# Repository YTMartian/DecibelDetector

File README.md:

# ESP32-C3 数字分贝检测器（INMP441 + 74HC595）

**PCB REV4 集成版 · 固件 v2.2 · 探测程序 v3 · 2026-10**

> **定位**：DIY 环境噪声监测与学习项目。它输出的是**估算 dB(A)**，不是经检定/校准的标准声级计，不能用于噪声合规判定或法律用途。

## 快速开始

1. 把 ESP32-C3 插进 U1-L/U1-R 两个 2×8 母座：**USB-C 朝下、芯片朝自己、5V 在左下角**。显示屏装到正面 JDISP_IN / JDISP_AUX，麦克风装到背面 JMIC。**先核对显示屏 5 脚顺序**（板上丝印：`LCD: CHECK INPUT PAD ORDER`），接反 VCC/GND 可能损坏模块。
2. Arduino IDE：安装 `esp32 by Espressif Systems` 3.x，板子选 `ESP32C3 Dev Module`，**Tools → USB CDC On Boot → Enabled**。
3. 烧 `firmware/Display_595_Probe`，看数码管：每组 profile 先显示 `1234`，再显示四位 `0/1`。找到 `1234` 正确的那组，记下四位。
4. 把四位填进主程序的四个 `constexpr bool`，必要时再填 `SEGMENT_MAP`，烧 `firmware/SoundMeter_595_ESP32C3`。
5. 接上麦克风，串口应出现 `A_est` / `Z_est` / `rmsA` / `rmsZ`；说话或拍手时数值应明显变化。

## 1. 能做什么

- INMP441 以 I²S **48 kHz、32-bit 槽、立体声**采集；`L/R` 接地，只使用左声道。
- ESP32-C3 计算**估算 A 计权声级**（dB(A)）和未计权声压级（Z），每 0.5 s 刷新四位数码管，同时从串口输出 A/Z/RMS。
- 显示驱动是**两片级联 74HC595**（一片段码、一片位选），不是 TM1637；不需要 TM1637 库。
- 显示极性、字节顺序、数字左右顺序、段码脚位都可配置；附带探测程序帮助确定。
- PCB 为**半集成载板**：ESP32 仍插在正面 2×8 母座；显示屏和麦克风直接装在 PCB 的焊盘/插座上，不再使用 J1/J2 短线。USB-C 从底边缺口朝外，麦克风在背面拾音。

## 2. 当前状态

| 项目 | 状态 |
|---|---|
| 显示屏 + 595 驱动 | 实物调通 |
| INMP441 I²S 采集 | 实物调通 |
| 串口 A/Z/RMS 输出 | 实物调通（需 `USB CDC On Boot = Enabled`） |
| 绝对声压级校准 | **未做**，`CALIBRATION_OFFSET_DB = 0` |
| PCB REV4 打样 / KiCad DRC / 嘉立创 DFM | **未做** |
| 外壳、USB 插头外壳宽度、排针高度 | **未实测** |

测量不确定度主要来自：INMP441 灵敏度公差 ±3 dB、约 33 dB(A) 的等效输入噪声、近似的 A 计权、未校准、供电/显示耦合。**不要把绝对读数和标准限值直接比较。**

## 3. 硬件

### 3.1 物料

| 材料 | 数量 | 说明 |
|---|---:|---|
| ESP32-C3 SuperMini | 1 | USB-C，优先已焊排针版 |
| INMP441 I²S 麦克风模块 | 1 | 6 引脚，**只用 3.3V** |
| 四位 LED 数码管模块 | 1 | 两片 74HC595 级联；按实物引脚 |
| PCB REV4 | 1 | 81.28 × 60.96 mm，双层 1.6 mm |
| 1×8 母排针 | 2 | 2.54 mm，排距 15.24 mm |
| 1×5 母排针 | 2 | 显示屏两排 5 孔 |
| 6 根短线或对应插座 | 1 | 麦克风 JMIC（2×3 焊盘） |
| M2.2 螺丝 + 绝缘柱 | 4 | 显示屏定位 |
| M3 螺丝 + 绝缘柱 | 4 | 主板固定 |
| 杜邦线 | 若干 | 显示屏/麦克风转接 |
| USB-C **数据**线 | 1 | 能烧录的线 |
| 100 nF + 10 µF | 可选 | 供电/显示干扰大时加在 3.3V 附近 |

本项目没有独立的 `BOM.csv`/`netlist.csv`；板级连接以 PCB 丝印和本文表格为准，具体排针/座子按你手里的模块选。

### 3.2 显示屏：JDISP_IN / JDISP_AUX

正面显示屏区域有两排 5 孔：

- 右侧 **JDISP_IN** 是电气连接（从上到下）：

  | JDISP_IN | 信号 | ESP32-C3 |
  |---:|---|---|
  | 1 | VCC | 3V3 |
  | 2 | SCLK | GPIO7 |
  | 3 | RCLK | GPIO10 |
  | 4 | DIO | GPIO3 |
  | 5 | GND | GND |

- 左侧 **JDISP_AUX** 的 5 个孔**没有连接任何网络**，只作机械支撑/备用；不要把它当电源或信号。
- 四角有 4 个 **M2.2** 定位孔，对应显示屏模块的安装柱。

> **板上丝印明确写着 `LCD: CHECK INPUT PAD ORDER`。** 插屏前逐脚核对显示模块的 5 脚顺序是否与 `VCC/SCLK/RCLK/DIO/GND` 一致；不一致必须做转接/换线序，**不能硬插**，否则可能把 VCC 和 GND 接反。

### 3.3 麦克风：背面 JMIC

背面 `JMIC` 是 2×3 焊盘，按背面丝印逐脚连接：

| 位置 | 信号 | ESP32-C3 |
|---|---|---|
| 上排 | GND | GND |
| 上排 | VDD | 3V3 |
| 上排 | SD | GPIO6 |
| 下排 | L/R | GND |
| 下排 | WS | GPIO5 |
| 下排 | SCK | GPIO4 |

- INMP441 的 `L/R` 必须接 GND（选左声道）；悬空会导致声道错位或无声。
- 麦克风装在**背面**，声孔朝外；丝印：`MIC BACK ONLY` / `PORT FACES OUT`。
- 如果模块引脚间距和 JMIC 不一致，用短线按丝印连接，不要强行弯脚。

### 3.4 ESP32-C3 安装方向（关键）

拿起 PCB **正面朝自己，USB-C 指向下方底边的缺口**，开发板的**芯片也朝自己**。此时两侧从上到下的引脚应为：

| 排针位置 | 左侧 U1-L | 右侧 U1-R |
|---:|---|---|
| 1 | GPIO0 | GPIO21 |
| 2 | GPIO1 | GPIO20 |
| 3 | GPIO2 | GPIO10 |
| 4 | GPIO3 | GPIO9 |
| 5 | GPIO4 | GPIO8 |
| 6 | 3V3 | GPIO7 |
| 7 | GND | GPIO6 |
| 8 | 5V（不接） | GPIO5 |

即 **5V 应落在左下角**。安装前按实物丝印再确认一次；插反可能把 5V 灌到 GPIO/3V3，损坏模块。

### 3.5 电源与地

- INMP441 和显示逻辑都用 **3.3V**；不要把 5V 接到 INMP441 或显示模块的信号侧。
- 显示模块即使标称 5V，也优先用 3.3V 测试：亮度会低一些，但 GPIO 电平安全。
- 所有模块共地；电源轨先确认导通。
- 5V 焊盘不接任何模块，板子由 ESP32 的 USB-C 供电。

## 4. PCB REV4（集成版）

- 外形：**81.28 × 60.96 mm**，双层 FR-4，1.6 mm，1 oz 铜。
- USB-C 避让缺口：底边 `x = 34.036～46.228 mm`，`y = 53.340～60.960 mm`，即 **12.192 × 7.620 mm**；缺口在 ESP32 正下方。
- 4 个 M3 孔：`(5.08,5.08)`、`(76.2,5.08)`、`(5.08,55.88)`、`(76.2,55.88)`，直径 3.2 mm。
- 显示屏 4 个 M2.2 孔：`(20.32,8.636)`、`(20.32,25.908)`、`(54.864,8.636)`、`(54.864,25.908)`。
- 显示屏两排 5 孔：右侧 `JDISP_IN`（电气）与左侧 `JDISP_AUX`（未连网络），孔距 2.54 mm。
- ESP32 2×8 母座：排距 15.24 mm，同列 2.54 mm，钻孔 1.0 mm。
- 麦克风 `JMIC`：背面 2×3 焊盘，2.54 mm 间距，两排相距 7.62 mm。

文件：

- `source/SoundMeter_Integrated_C3_595_REV4.kicad_pcb`：可编辑 KiCad PCB（**不含** `.kicad_sch` 原理图）。
- `gerber/`：9 个 Gerber / 钻孔文件，KiCad 默认命名（`SoundMeter-F_Cu.gtl`、`-B_Cu.gbl`、`-F_Mask.gts`、`-B_Mask.gbs`、`-F_Silkscreen.gto`、`-B_Silkscreen.gbo`、`-Edge_Cuts.gko`、`-PTH.drl`、`-NPTH.drl`）。
- `Gerber_打样前先核对.zip`：上面 9 个文件打好的包，可直接上传嘉立创。
- `preview/Integrated_PCB_Front_Back.png`：正反面安装预览。

> **REV4 相对 v3**：显示屏和麦克风改为板载安装，不再有 J1/J2 短线；板深从 55.88 增加到 60.96，USB 缺口移到 ESP32 下方并加深到 7.62 mm。**不能复用 v3 的 Gerber。**

制板前：

1. 在 KiCad 里跑一次官方 **DRC**；本项目尚未跑过。
2. 上传 Gerber 到嘉立创后，在 2D/3D 预览确认 **USB 缺口被识别成单块异形板**、钻孔和焊盘完整。
3. 用实物 USB-C 插头核对缺口宽度（约 12.19 mm）和插头塑胶外壳；用实物排针核对 ESP32 插座高度。
4. 用实物显示屏核对两排 5 孔的间距和 4 个 M2.2 定位孔；**先核对 5 脚顺序**。
5. 嘉立创参数：双层、FR-4、1.6 mm、1 oz、绿色阻焊、常规表面处理；**不贴片**，手工焊排针/母座。

## 5. 软件环境

- **Arduino IDE 2.x**。
- 开发板核心：`esp32 by Espressif Systems` **3.x**（3.0 及以上）。
- 开发板：`ESP32C3 Dev Module`。
- **Tools → USB CDC On Boot → Enabled**（关键）。
- 不需要 TM1637 库；`ESP_I2S.h` 随 ESP32 核心提供。
- 串口监视器 115200（原生 USB CDC 的“波特率”实际不影响通信，保持默认即可）。

### 为什么必须开 USB CDC On Boot

ESP32-C3 SuperMini 没有 CH340/CP2102，USB-C 直接接芯片内置的 **USB Serial/JTAG**：

| 设置 | `Serial` 连到 | 结果 |
|---|---|---|
| **Enabled** | USB Serial/JTAG（GPIO18/19） | 电脑出现虚拟串口，`Serial.print` 能到监视器 |
| Disabled | UART0（GPIO20/21） | USB 口收不到应用输出；监视器全空，发字符还可能把 IDE/USB 卡住 |

这是**编译期选项**（`ARDUINO_USB_CDC_ON_BOOT`），改完必须**重新上传**。打开后 COM 号可能变化，重新选端口；先打开串口监视器再按 RST，能抓到启动日志。

> 固件里的串口输出已改成**非阻塞**：监视器没开或端口不对时只是丢数据，不会再把设备卡死。但 `USB CDC On Boot` 仍然要开，否则根本收不到数据。

## 6. 调试步骤

### 6.1 只装显示屏：`Display_595_Probe`

先不装麦克风，烧 `firmware/Display_595_Probe`（显示屏装到 JDISP_IN，JDISP_AUX 可空）。

- 16 组 profile 自动轮换，每组 2.5 s：
  - 前 **1.0 s** 显示 `1234`；
  - 后 **1.5 s** 显示四位 `0/1`，顺序为：

    ```text
    SEG_LOW  DIGIT_HIGH  SEG_FIRST  REVERSE
    ```

- 看到 `1234` 从左到右正确显示时，记下紧接着的四位。例如显示 `1 0 1 0`：

  ```cpp
  constexpr bool SEGMENT_ACTIVE_LOW = true;
  constexpr bool DIGIT_ACTIVE_HIGH  = false;
  constexpr bool SEGMENT_FIRST      = true;
  constexpr bool REVERSE_DIGITS     = false;
  ```

- 如果 `1234` 显示成 `4321`，按 `4` 翻转 `REVERSE_DIGITS`；如果四位全亮，按 `2` 翻转位极性；如果七段全亮，按 `1` 翻转段极性；如果段和位明显串了，按 `3` 翻转字节顺序。

**段码脚位不是标准 Q0=a…Q7=dp 时**：

- 串口发 `s` 进入段扫描，每 1.5 s 换一个原始段输出 `Q0…Q7`；
- 记下每个 `Qn` 实际点亮的是 `a/b/c/d/e/f/g/dp` 哪一段；
- 填主程序的 `SEGMENT_MAP`（方向是**逻辑段 → Q 编号**）：

  ```cpp
  // 例：Q0→dp, Q1→g, Q2→f, Q3→e, Q4→d, Q5→c, Q6→b, Q7→a
  constexpr uint8_t SEGMENT_MAP[8] = {7,6,5,4,3,2,1,0};
  ```

- 串口不可用时，数码管仍会自动显示四位的 profile 结果，**不依赖串口输入**；段扫描才需要串口命令。

可选串口命令：

| 键 | 作用 |
|---|---|
| `1` | 翻转 `SEGMENT_ACTIVE_LOW` |
| `2` | 翻转 `DIGIT_ACTIVE_HIGH` |
| `3` | 翻转 `SEGMENT_FIRST` |
| `4` | 翻转 `REVERSE_DIGITS` |
| `s` | 段扫描 Q0～Q7 |
| `d` | 位扫描 D0～D3 |
| `x` | 冻结当前 profile |
| `p` | 重新开始自动轮换 |
| `h` | 帮助 |

### 6.2 烧主程序：`SoundMeter_595_ESP32C3`

1. 把 6.1 得到的四个常量填进主程序顶部；非标准段序再填 `SEGMENT_MAP`。
2. 烧录。上电会显示 `8888` 约 0.5 s，然后清屏；前 1 秒是滤波器预热，约 1.5 秒后出第一个数。
3. 串口应出现类似：

```text
ESP32-C3 / INMP441 / 74HC595 sound meter (estimated, not certified)
Display profile: segmentLow=1 digitHigh=1 segmentFirst=1 reverseDigits=0
Segment map a..dp -> Q0,1,2,3,4,5,6,7
Sound display: estimated dB(A), rate=48000Hz, calibration offset=0.0 dB
A_est=62.3 dB(A)  Z_est=64.7 dB SPL  rmsA=0.000...  rmsZ=0.000...
```

4. 装好麦克风，对着它说话或拍手：`rmsZ` 应明显变化，`A_est`/`Z_est` 跟着上升。安静房间读数大约 30～40 dB(A) 是正常的（INMP441 自噪声约 33 dB(A)），不要强行清零。

### 6.3 串口没有输出 / IDE 卡住

1. 确认 **Tools → USB CDC On Boot = Enabled**，重新上传。
2. 拔插 USB，重新选 COM 口；ESP32-C3 原生 USB 有时会出现两个端口，换另一个试。
3. 先打开串口监视器，再按板子 RST（或拔插 USB），让启动横幅在监视器已打开时打印。
4. 确认选的是应用的 USB CDC 口，而不是下载模式/其他串口。
5. 如果旧版 ESP32 核心在输入字符时仍卡住：升级到最新 3.x（新版 `HWCDC` 对 USB 写有超时保护）；或干脆不发串口命令，直接用数码管显示的四位 profile。

## 7. 固件配置

修改 `firmware/SoundMeter_595_ESP32C3/SoundMeter_595_ESP32C3.ino` 顶部后重新编译上传：

| 常量 | 默认 | 说明 |
|---|---|---|
| `SEGMENT_ACTIVE_LOW` | `true` | 段输出低电平点亮 |
| `DIGIT_ACTIVE_HIGH` | `true` | 位选高电平点亮 |
| `SEGMENT_FIRST` | `true` | 先发送段码字节 |
| `REVERSE_DIGITS` | `false` | 位选 bit3 为最左位 |
| `SEGMENT_MAP[8]` | `{0,1,2,3,4,5,6,7}` | 逻辑 `a..dp` → 原始 `Q0..Q7` |
| `SHOW_A_WEIGHTED` | `true` | `true` 显示 A 计权；`false` 显示未计权 |
| `CALIBRATION_OFFSET_DB` | `0.0` | 没有参考仪器时保持 0 |
| `SAMPLE_RATE_HZ` | `48000` | A 计权系数按 48 kHz 设计 |
| `DISPLAY_INTERVAL_MS` | `500` | 显示/统计窗口 |

**不要单独把 `SAMPLE_RATE_HZ` 改成 16000 或 32000** 而不重新设计 A 计权 SOS 系数；滤波器系数与采样率绑定。需要 LAeq/峰值/长时间平均时，应改统计窗口与算法，而不是改采样率。

## 8. 分贝是怎么算出来的

INMP441 手册：1 kHz、94 dB SPL 正弦，灵敏度典型 **−26 dBFS**（−29 / −26 / −23 dBFS，±3 dB）；该 dBFS 按**峰峰值**相对满量程定义。对正弦，归一化 RMS 为：

```text
RMS_94 = 10^(-26/20) / sqrt(2) ≈ 0.035439
SPL_est = 94 + 20*log10(RMS / RMS_94) + CALIBRATION_OFFSET_DB
```

- 32 位 I²S 槽里的 24 位有符号数据左对齐，`sample / 2^31` 归一化到约 −1～1。
- 除以 √2 很关键：把峰值当 RMS 会差约 3.01 dB。
- A 计权用 3 个二阶 IIR 节（SOS）近似，1 kHz 归一到 0 dB；48 kHz 下与 IEC A 计权在 8 kHz 以内偏差约 0.5 dB 以内，12 kHz 约 −2.3 dB、16 kHz 约 −6.4 dB（双线性变换的高频误差）。它是**近似实现**，不等于标准声级计。
- 未计权路径只做了一阶 DC 去除，不是标准 Z 计权。
- 典型自噪声 33 dB(A)，灵敏度 ±3 dB；没有参考仪器时，绝对读数只能当估算值。

### 校准与“最低 46 dB”

- 没有声级计/94 dB 声校准器时，`CALIBRATION_OFFSET_DB` 保持 0；不要把手机 App 当校准基准（手机麦克风也有偏差）。
- 46 dB(A) 在普通居家环境不算异常：安静卧室 30～40，普通客厅/书房 40～50，有电脑风扇/冰箱/空调 45～55。
- 想判断是环境声还是设备电噪：轻轻捂住麦克风声孔（读数明显下降=环境声）；换房间/关电器；断开显示屏再测（明显下降=显示/供电耦合）；换 USB 供电（充电宝 vs 电脑）。
- 显示的是 0.5 s 的瞬时 A 计权值，不是长时间最小值；观察时间太短会把间歇声当成“底噪”。

## 9. 常见问题

| 现象 | 可能原因 | 处理 |
|---|---|---|
| 烧录找不到 COM | 线是充电线、驱动、启动模式 | 换数据线 → 选端口 → 按住 BOOT 再复位 |
| 串口全空 | `USB CDC On Boot` 未开、端口错 | 开 CDC、重新上传、重选端口 |
| 输入字符后 IDE 卡死 | 旧核心 USB CDC 写阻塞 | 升级核心；本版固件已非阻塞；用数码管读 profile |
| 开机不显示 | 显示不是两片 595、供电/接线错 | 先烧探测程序，查 VCC/GND/SCLK/RCLK/DIO |
| 数码管乱码 | profile 不对、段序非标准 | 用 `1234`+四位 bits 找 profile；`s` 段扫描填 `SEGMENT_MAP` |
| 数字左右反了 | `REVERSE_DIGITS` 反 | 按 `4` 或改常量 |
| 只有一位亮 / 四位全亮 | 位极性/位选错 | 按 `2`、`d` 位扫描 |
| 数字很暗 | 3.3V 供电、模块按 5V 设计 | 确认允许 3.3V；不要为亮度把逻辑接 5V |
| `FATAL: I2S setup failed` | 核心版本/引脚/资源 | 核心 3.x、ESP32C3 Dev Module、检查 GPIO4/5/6 |
| `ERROR: no I2S samples` | 麦克风焊盘/连线断、`L/R` 错、供电 | 查 VDD/GND/SCK/WS/SD，`L/R` 接 GND |
| `audio near-zero` | 左声道没数据、`L/R` 悬空、声孔堵 | 查 `L/R`、SD、麦克风声孔 |
| 安静时总有 30 多 dB | INMP441 自噪声 | 正常限制，不应清零 |
| 读数偏高/偏低 | 未校准 ±3 dB、电噪、低频环境声 | 看 `Z_est`；做第 8 节的三步测试 |
| 显示闪烁 | 刷新任务被阻塞/供电不稳 | 确认单核任务正常运行；查 3.3V 和 GND |
| 上电重启/数字乱闪 | USB 电源、接触不良、屏电流大 | 换 USB 口/线，降低亮度（硬件），查电源轨 |

## 10. 文件结构

```text
DecibelDetector/
├── README.md
├── .gitignore
├── Gerber_打样前先核对.zip
├── firmware/
│   ├── Display_595_Probe/
│   │   └── Display_595_Probe.ino
│   └── SoundMeter_595_ESP32C3/
│       └── SoundMeter_595_ESP32C3.ino
├── gerber/
│   ├── SoundMeter-F_Cu.gtl
│   ├── SoundMeter-B_Cu.gbl
│   ├── SoundMeter-F_Mask.gts
│   ├── SoundMeter-B_Mask.gbs
│   ├── SoundMeter-F_Silkscreen.gto
│   ├── SoundMeter-B_Silkscreen.gbo
│   ├── SoundMeter-Edge_Cuts.gko
│   ├── SoundMeter-PTH.drl
│   └── SoundMeter-NPTH.drl
├── preview/
│   └── Integrated_PCB_Front_Back.png
└── source/
    └── SoundMeter_Integrated_C3_595_REV4.kicad_pcb
```

> 每个 `.ino` 必须放在同名文件夹里，Arduino IDE 才能直接打开。

## 11. 制板与装配注意

- **USB 缺口**约 12.19 mm 宽、7.62 mm 深；部分 USB-C 线材的塑胶外壳更宽，打样前用实物插头 1:1 比对，必要时加宽缺口后重新导出 Gerber。
- ESP32 排针高度、USB 母座到模块底边的偏移量未实测；装配前先空板试插。
- **显示屏 5 脚顺序**必须逐脚核对（板上丝印已经提醒）；`JDISP_AUX` 不连网络，只作机械支撑。
- 麦克风装在背面，声孔朝外并对外壳开孔；**不要用热熔胶/导电胶覆盖**。
- 显示屏/麦克风若用短线转接，线长 10～20 cm 以内；I²S BCLK 为 3.072 MHz，线太长容易出错。
- 显示/麦克风供电不稳时，在 3.3V 与 GND 之间加 100 nF + 10 µF 去耦；麦克风地线尽量单独回板。
- 板子用 M3 绝缘柱固定，显示屏用 M2.2 柱固定；避免麦克风与数码管/外壳机械振动耦合。

## 12. 参考

1. [TDK / InvenSense INMP441 数据手册](https://product.tdk.com/system/files/dam/doc/product/sw_piezo/mic/mems-mic/data_sheet/inmp441.pdf) — 灵敏度、24 位左声道 I²S、3.2 MHz 上限、dBFS 定义。
2. [Espressif Arduino-ESP32 I²S API](https://docs.espressif.com/projects/arduino-esp32/en/latest/api/i2s.html) — `ESP_I2S.h`、`setPins`、`begin`、`readBytes`。
3. [TI SN74HC595 数据手册](https://www.ti.com/lit/ds/symlink/sn74hc595.pdf) — 移位寄存器/锁存时序。
4. [Apache NuttX ESP32-C3 SuperMini 引脚文档](https://github.com/apache/nuttx/blob/master/Documentation/platforms/risc-v/esp32c3/boards/esp32c3-supermini/index.rst) — SuperMini 排针位置参考。

## 13. 免责声明

本项目是学习/DIY 项目，**不是**经检定或校准的声级计，不满足 IEC 61672 Class 1/2，不能用于噪声合规、职业健康或法律用途。作者不对因使用本项目造成的任何损失负责。测量结果受麦克风个体差异、供电、结构、校准和环境声影响；需要准确声压级时，请使用经过校准的声级计。

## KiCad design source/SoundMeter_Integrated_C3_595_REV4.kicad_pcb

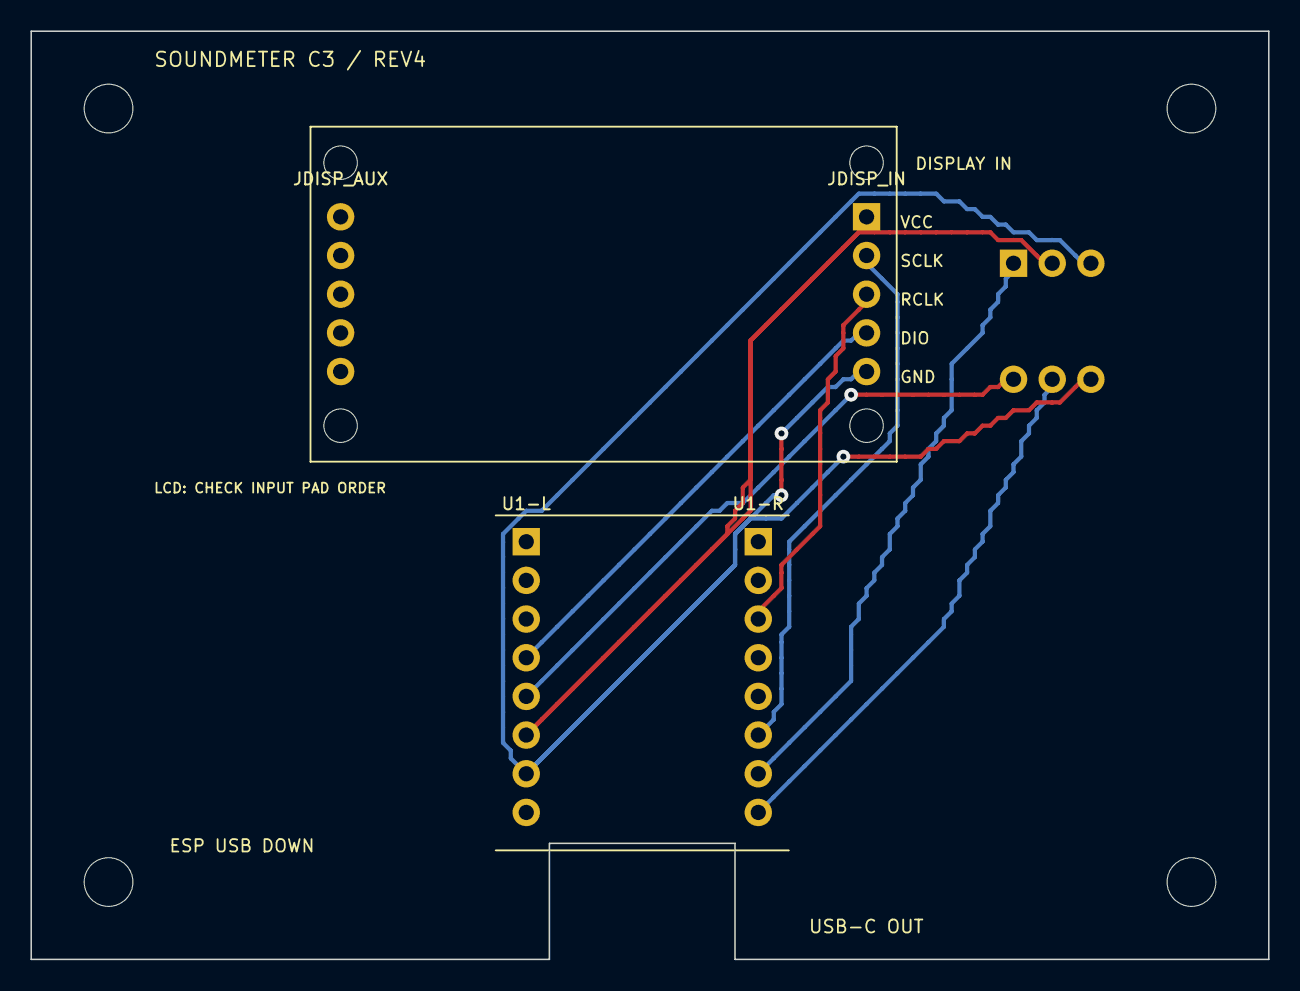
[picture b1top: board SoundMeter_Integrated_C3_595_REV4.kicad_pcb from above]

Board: 2 copper layers, 81.3 x 61.0 mm, 13 parts (1 on the bottom side), 8 nets.

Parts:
D-M2-00, D-M2-01, D-M2-10, D-M2-11: MountingHole_2.2mm
H1, H2, H3, H4: MountingHole_3.2mm
JDISP_AUX: MODULE_SOCKET; JDISP_AUX
JDISP_IN: MODULE_SOCKET; JDISP_IN
JMIC: MODULE_SOCKET; JMIC
U1-L: MODULE_SOCKET; U1-L
U1-R: MODULE_SOCKET; U1-R

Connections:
3V3: JDISP_IN.VCC, JMIC.VDD, U1-L.3V3
DATA595: JDISP_IN.DIO, U1-L.GPIO3
GND: JDISP_IN.GND, JMIC.GND, JMIC.L/R, U1-L.GND
MIC_SCK: JMIC.SCK, U1-L.GPIO4
MIC_SD: JMIC.SD, U1-R.GPIO6
MIC_WS: JMIC.WS, U1-R.GPIO5
RCLK595: JDISP_IN.RCLK, U1-R.GPIO10
SCLK595: JDISP_IN.SCLK, U1-R.GPIO7

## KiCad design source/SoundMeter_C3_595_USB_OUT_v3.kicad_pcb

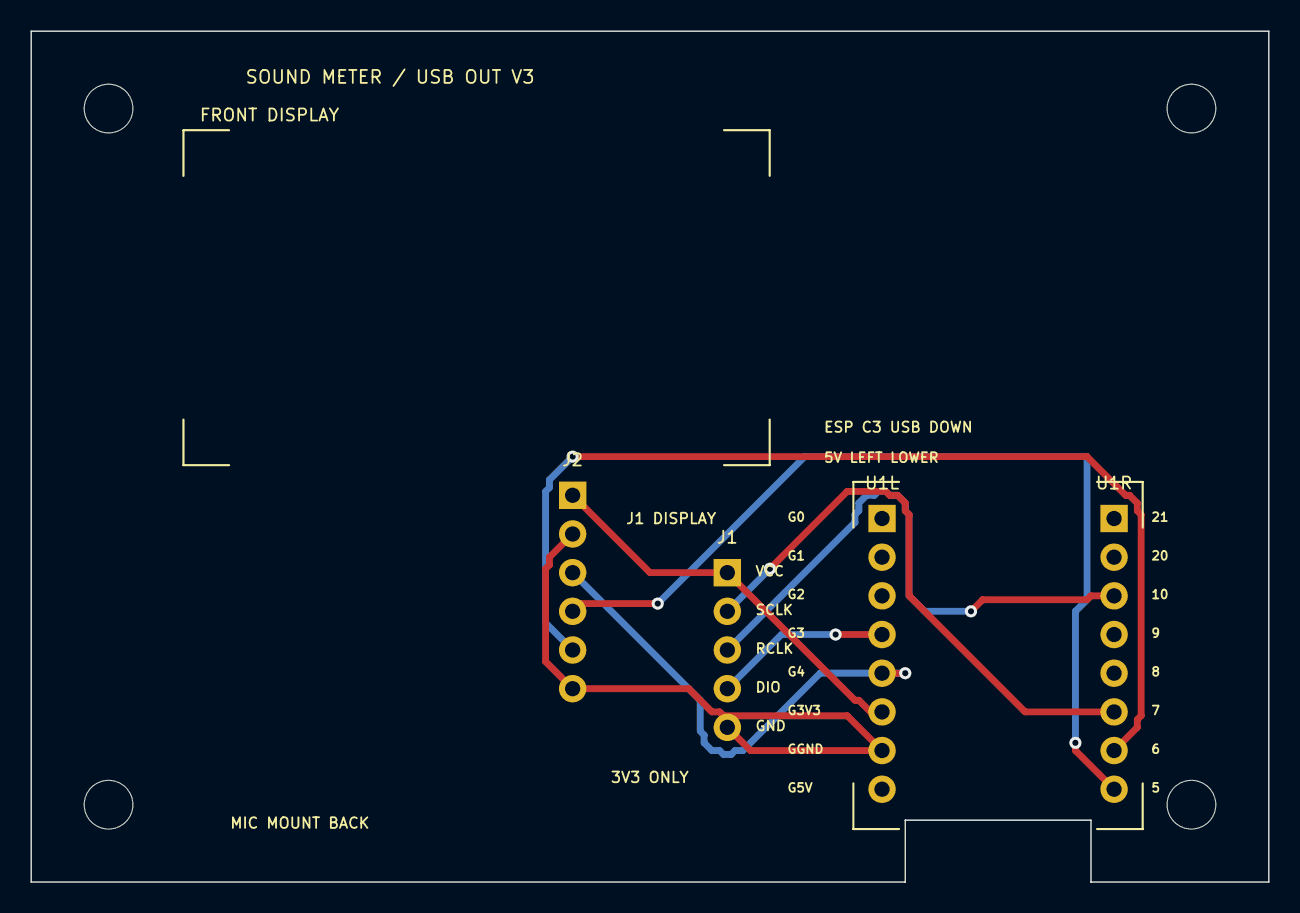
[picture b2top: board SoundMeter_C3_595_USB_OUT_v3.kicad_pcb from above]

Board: 2 copper layers, 81.3 x 55.9 mm, 8 parts (0 on the bottom side), 8 nets.

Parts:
H1, H2, H3, H4: MountingHole_3.2mm_M3
J1: DISPLAY_595_FRONT_CABLE; PinHeader_1x05_P2.54mm_Vertical
J2: INMP441_BACK_CABLE; PinHeader_1x06_P2.54mm_Vertical
U1L: ESP_C3_LEFT_GPIO; PinHeader_1x08_P2.54mm_Vertical
U1R: ESP_C3_RIGHT_PWR; PinHeader_1x08_P2.54mm_Vertical

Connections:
3V3: J1.1, J2.1, U1L.6
DATA595: J1.4, U1L.4
GND: J1.5, J2.2, J2.6, U1L.7
RCLK595: J1.3, U1R.3
SCKMIC: J2.3, U1L.5
SCLK595: J1.2, U1R.6
SD: J2.5, U1R.7
WS: J2.4, U1R.8

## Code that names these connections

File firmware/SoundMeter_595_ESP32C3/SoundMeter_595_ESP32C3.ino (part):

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#include <stdio.h>
#include <string.h>

constexpr int PIN_MIC_SCK=4, PIN_MIC_WS=5, PIN_MIC_SD=6;
constexpr uint8_t PIN_DISP_SCLK=7, PIN_DISP_RCLK=10, PIN_DISP_DIO=3;

// ---- Display-profile knobs: use values printed by Display_595_Probe ----
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  if(ok!=pdPASS){ serialPrintln("FATAL: display task creation failed"); while(true)delay(1000); }
  delay(500);
  setGlyphs(FONT_BLANK,FONT_BLANK,FONT_BLANK,FONT_BLANK);
  mic.setPins(PIN_MIC_SCK,PIN_MIC_WS,-1,PIN_MIC_SD);
  if(!mic.begin(I2S_MODE_STD,SAMPLE_RATE_HZ,I2S_DATA_BIT_WIDTH_32BIT,
                I2S_SLOT_MODE_STEREO,I2S_STD_SLOT_BOTH)){
    serialPrintln("FATAL: I2S setup failed (ESP32 core 3.x?)");
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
